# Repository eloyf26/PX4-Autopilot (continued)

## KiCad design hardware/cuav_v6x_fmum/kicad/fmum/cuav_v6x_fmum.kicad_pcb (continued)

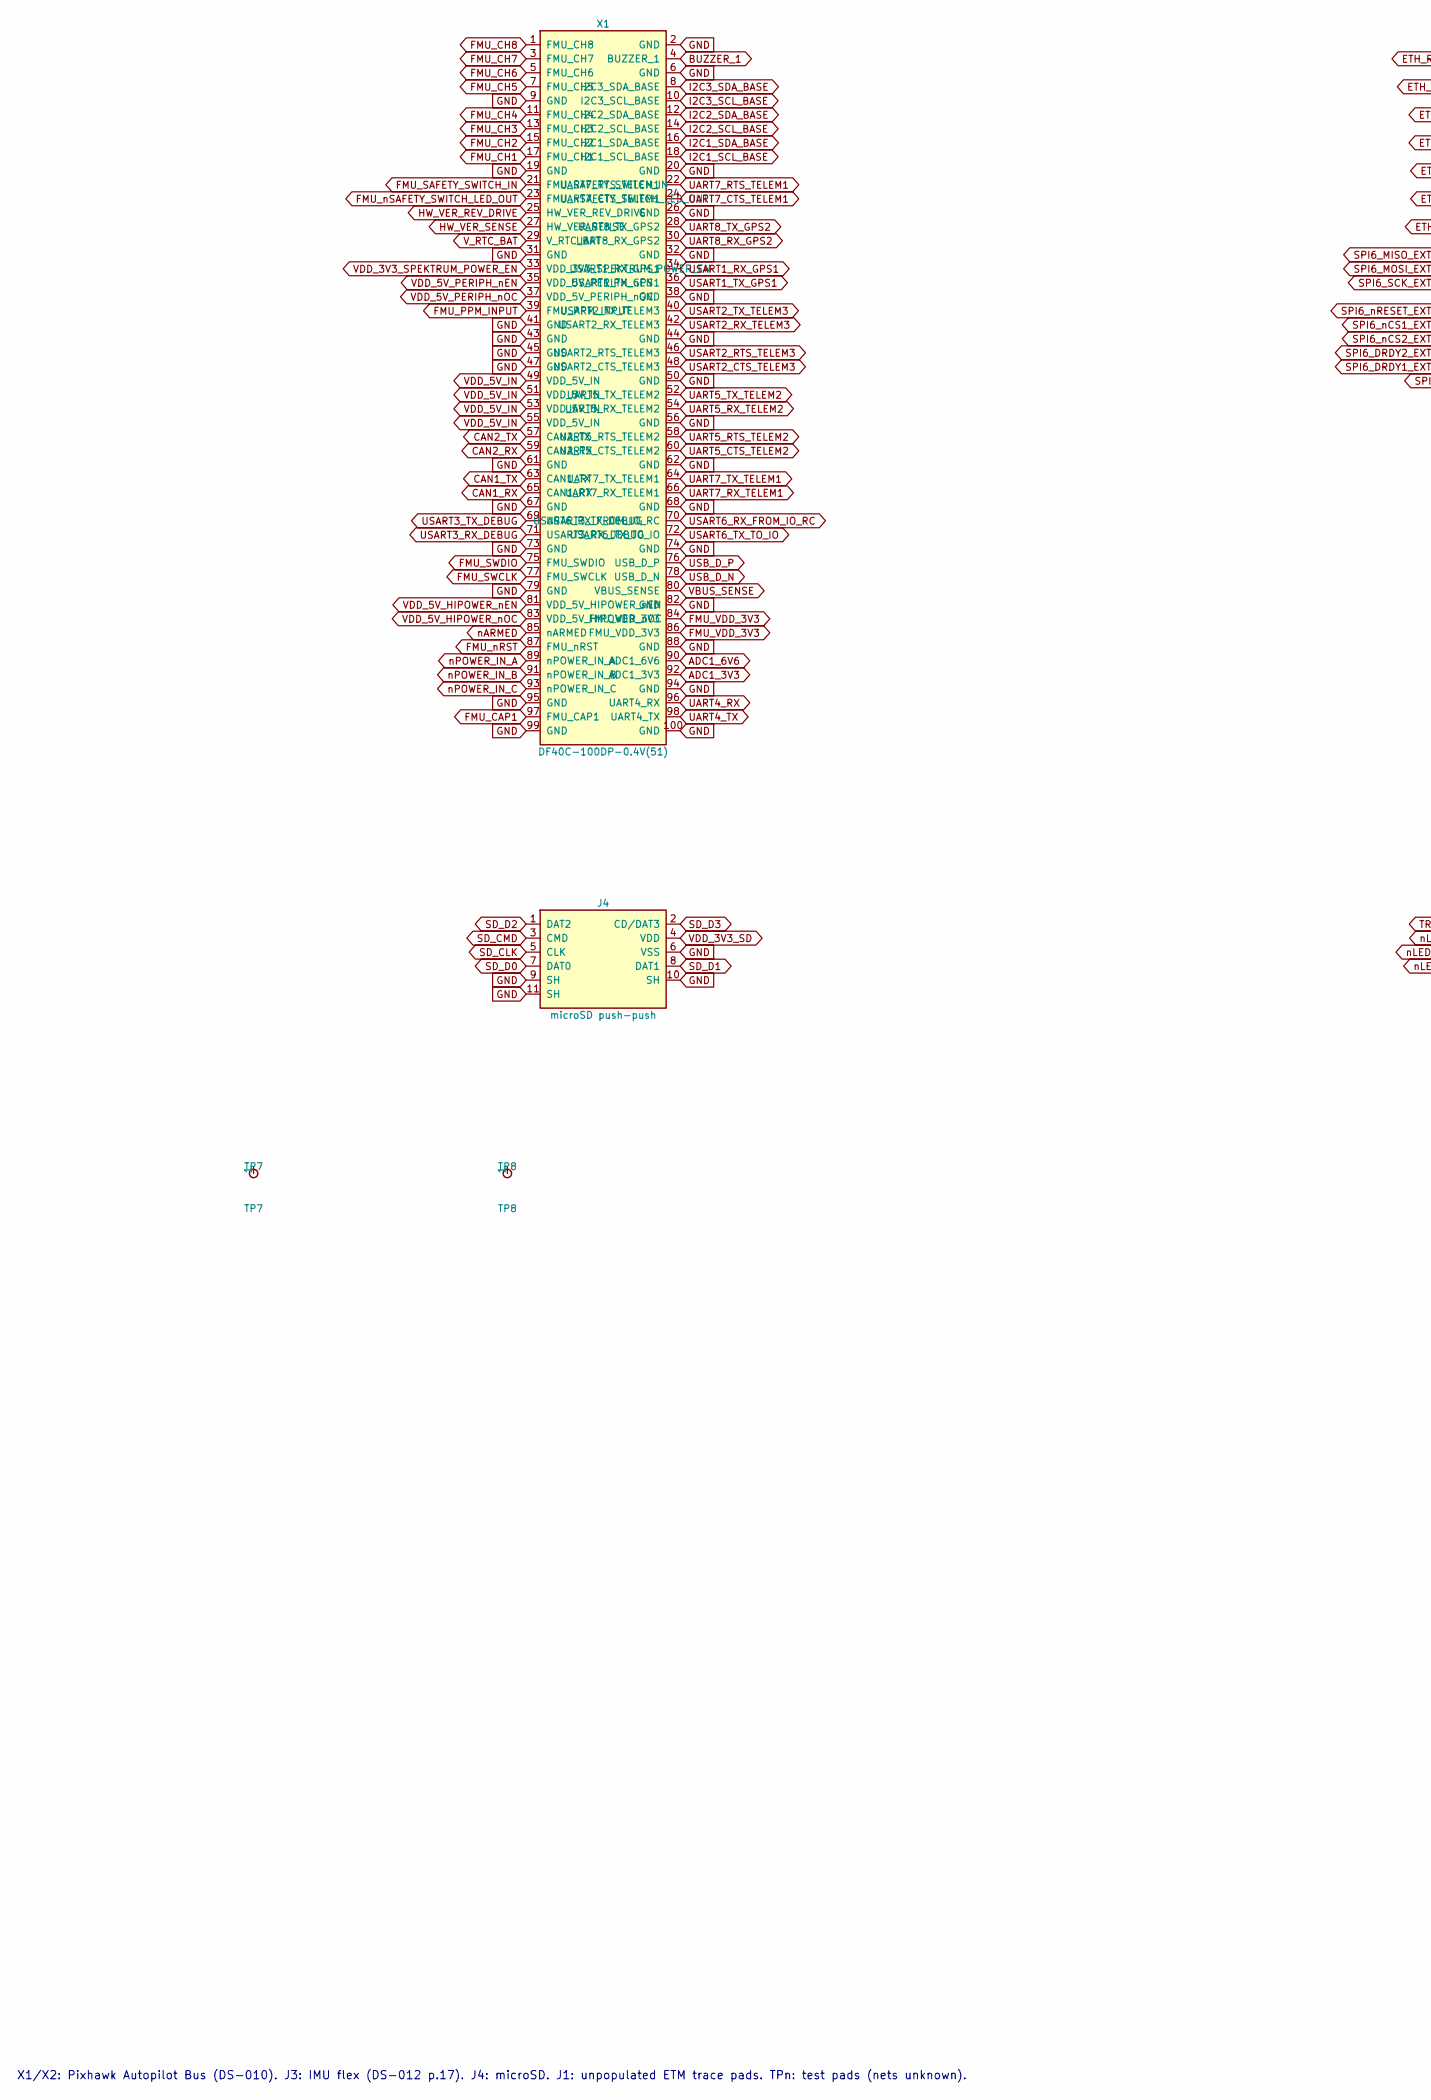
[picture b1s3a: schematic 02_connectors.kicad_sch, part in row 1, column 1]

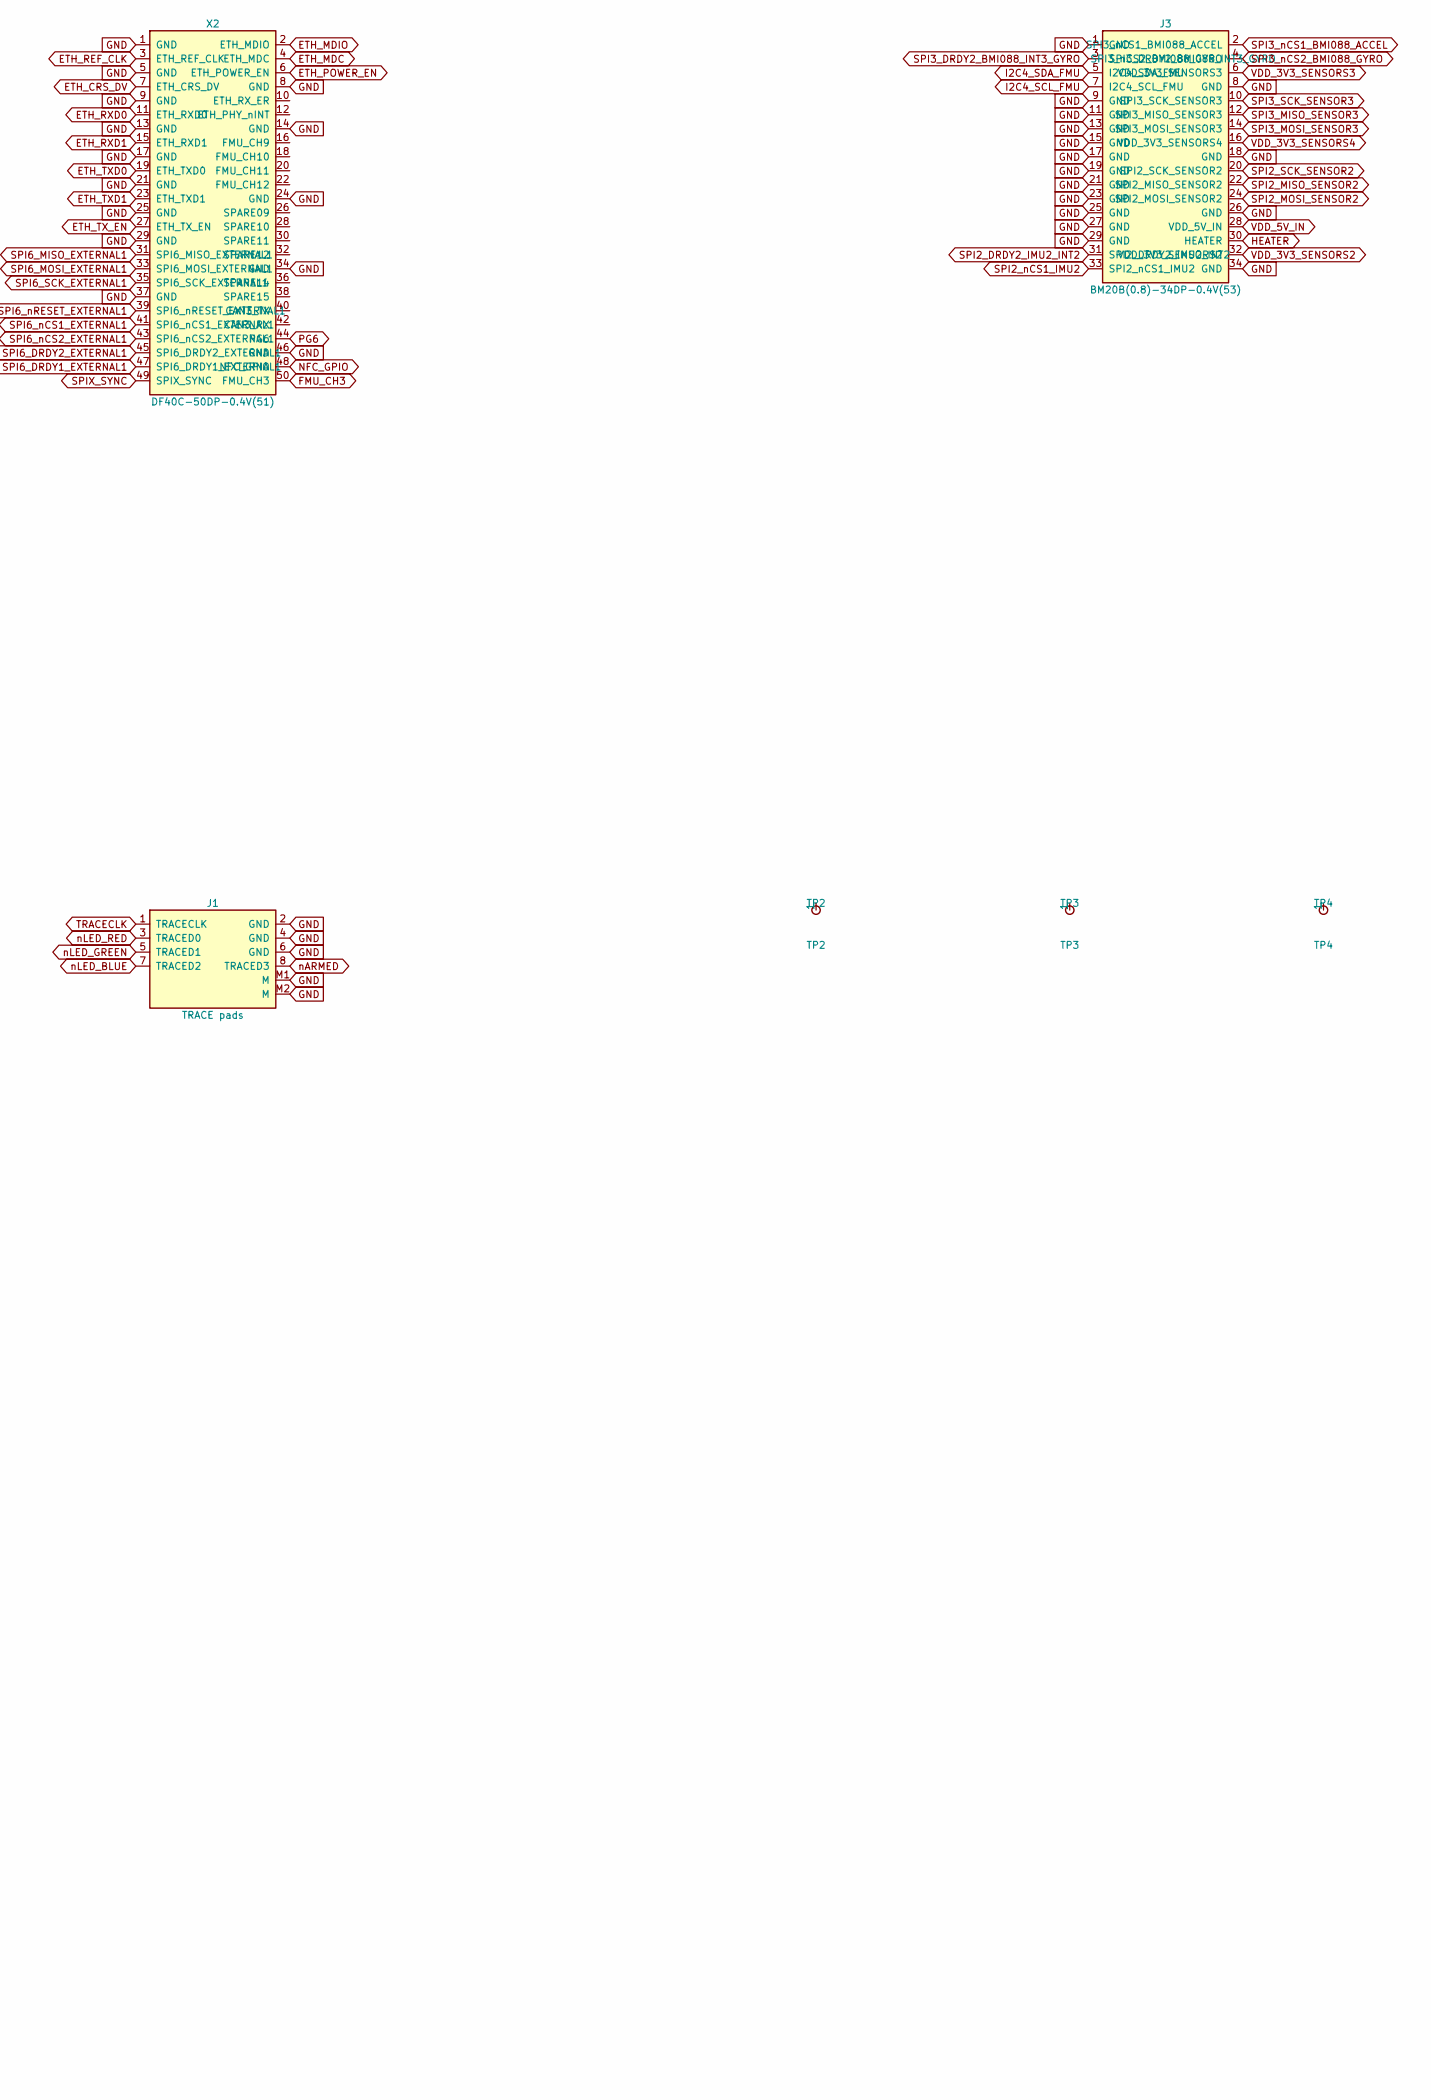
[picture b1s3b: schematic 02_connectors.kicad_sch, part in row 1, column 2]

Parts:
J1: TRACE pads; TRACE_8+2
J3: BM20B(0.8)-34DP-0.4V(53); Hirose_BM20B-34-0.4V
J4: microSD push-push; microSD_HC_Molex_104031-0811
TP2: TP2; TestPad_1.0mm
TP3: TP3; TestPad_1.0mm
TP4: TP4; TestPad_1.0mm
TP7: TP7; TestPad_1.0mm
TP8: TP8; TestPad_1.0mm
X1: DF40C-100DP-0.4V(51); Hirose_DF40C-100DP-0.4V
X2: DF40C-50DP-0.4V(51); Hirose_DF40C-50DP-0.4V

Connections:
ADC1_3V3: X1.92 (ADC1_3V3); also elsewhere on the board
ADC1_6V6: X1.90 (ADC1_6V6); also elsewhere on the board
BUZZER_1: X1.4 (BUZZER_1); also elsewhere on the board
CAN1_RX: X1.65 (CAN1_RX); also elsewhere on the board
CAN1_TX: X1.63 (CAN1_TX); also elsewhere on the board
CAN2_RX: X1.59 (CAN2_RX); also elsewhere on the board
CAN2_TX: X1.57 (CAN2_TX); also elsewhere on the board
ETH_CRS_DV: X2.7 (ETH_CRS_DV); also elsewhere on the board
ETH_MDC: X2.4 (ETH_MDC); also elsewhere on the board
ETH_MDIO: X2.2 (ETH_MDIO); also elsewhere on the board
ETH_POWER_EN: X2.6 (ETH_POWER_EN); also elsewhere on the board
ETH_REF_CLK: X2.3 (ETH_REF_CLK); also elsewhere on the board
ETH_RXD0: X2.11 (ETH_RXD0); also elsewhere on the board
ETH_RXD1: X2.15 (ETH_RXD1); also elsewhere on the board
ETH_TXD0: X2.19 (ETH_TXD0); also elsewhere on the board
ETH_TXD1: X2.23 (ETH_TXD1); also elsewhere on the board
ETH_TX_EN: X2.27 (ETH_TX_EN); also elsewhere on the board
FMU_CAP1: X1.97 (FMU_CAP1); also elsewhere on the board
FMU_CH1: X1.17 (FMU_CH1); also elsewhere on the board
FMU_CH2: X1.15 (FMU_CH2); also elsewhere on the board
FMU_CH3: X1.13 (FMU_CH3), X2.50 (FMU_CH3); also elsewhere on the board
FMU_CH4: X1.11 (FMU_CH4); also elsewhere on the board
FMU_CH5: X1.7 (FMU_CH5); also elsewhere on the board
FMU_CH6: X1.5 (FMU_CH6); also elsewhere on the board
FMU_CH7: X1.3 (FMU_CH7); also elsewhere on the board
FMU_CH8: X1.1 (FMU_CH8); also elsewhere on the board
FMU_PPM_INPUT: X1.39 (FMU_PPM_INPUT); also elsewhere on the board
FMU_SAFETY_SWITCH_IN: X1.21 (FMU_SAFETY_SWITCH_IN); also elsewhere on the board
FMU_SWCLK: X1.77 (FMU_SWCLK); also elsewhere on the board
FMU_SWDIO: X1.75 (FMU_SWDIO); also elsewhere on the board
FMU_VDD_3V3: X1.84 (FMU_VDD_3V3), X1.86 (FMU_VDD_3V3); also elsewhere on the board
FMU_nRST: X1.87 (FMU_nRST); also elsewhere on the board
FMU_nSAFETY_SWITCH_LED_OUT: X1.23 (FMU_nSAFETY_SWITCH_LED_OUT); also elsewhere on the board
GND: J1.2 (GND), J1.4 (GND), J1.6 (GND), J1.M1 (M), J1.M2 (M), J3.1 (GND), J3.8 (GND), J3.9 (GND), J3.11 (GND), J3.13 (GND), J3.15 (GND), J3.17 (GND), J3.18 (GND), J3.19 (GND), J3.21 (GND), J3.23 (GND), J3.25 (GND), J3.26 (GND), J3.27 (GND), J3.29 (GND), J3.34 (GND), J4.6 (VSS), J4.9 (SH), J4.10 (SH), J4.11 (SH), X1.2 (GND), X1.6 (GND), X1.9 (GND), X1.19 (GND), X1.20 (GND), X1.26 (GND), X1.31 (GND), X1.32 (GND), X1.38 (GND), X1.41 (GND), X1.43 (GND), X1.44 (GND), X1.45 (GND), X1.47 (GND), X1.50 (GND), X1.56 (GND), X1.61 (GND), X1.62 (GND), X1.67 (GND), X1.68 (GND), X1.73 (GND), X1.74 (GND), X1.79 (GND), X1.82 (GND), X1.88 (GND), X1.94 (GND), X1.95 (GND), X1.99 (GND), X1.100 (GND), X2.1 (GND), X2.5 (GND), X2.8 (GND), X2.9 (GND), X2.13 (GND), X2.14 (GND), X2.17 (GND), X2.21 (GND), X2.24 (GND), X2.25 (GND), X2.29 (GND), X2.34 (GND), X2.37 (GND), X2.46 (GND); also elsewhere on the board
HEATER: J3.30 (HEATER); also elsewhere on the board
HW_VER_REV_DRIVE: X1.25 (HW_VER_REV_DRIVE); also elsewhere on the board
HW_VER_SENSE: X1.27 (HW_VER_SENSE); also elsewhere on the board
I2C1_SCL_BASE: X1.18 (I2C1_SCL_BASE); also elsewhere on the board
I2C1_SDA_BASE: X1.16 (I2C1_SDA_BASE); also elsewhere on the board
I2C2_SCL_BASE: X1.14 (I2C2_SCL_BASE); also elsewhere on the board
I2C2_SDA_BASE: X1.12 (I2C2_SDA_BASE); also elsewhere on the board
I2C3_SCL_BASE: X1.10 (I2C3_SCL_BASE); also elsewhere on the board
I2C3_SDA_BASE: X1.8 (I2C3_SDA_BASE); also elsewhere on the board
I2C4_SCL_FMU: J3.7 (I2C4_SCL_FMU); also elsewhere on the board
I2C4_SDA_FMU: J3.5 (I2C4_SDA_FMU); also elsewhere on the board
NFC_GPIO: X2.48 (NFC_GPIO); also elsewhere on the board
PG6: X2.44 (PG6); also elsewhere on the board
SD_CLK: J4.5 (CLK); also elsewhere on the board
SD_CMD: J4.3 (CMD); also elsewhere on the board
SD_D0: J4.7 (DAT0); also elsewhere on the board
SD_D1: J4.8 (DAT1); also elsewhere on the board
SD_D2: J4.1 (DAT2); also elsewhere on the board
SD_D3: J4.2 (CD/DAT3); also elsewhere on the board
SPI2_DRDY2_IMU2_INT2: J3.31 (SPI2_DRDY2_IMU2_INT2); also elsewhere on the board
SPI2_MISO_SENSOR2: J3.22 (SPI2_MISO_SENSOR2); also elsewhere on the board
SPI2_MOSI_SENSOR2: J3.24 (SPI2_MOSI_SENSOR2); also elsewhere on the board
SPI2_SCK_SENSOR2: J3.20 (SPI2_SCK_SENSOR2); also elsewhere on the board
SPI2_nCS1_IMU2: J3.33 (SPI2_nCS1_IMU2); also elsewhere on the board
SPI3_DRDY2_BMI088_INT3_GYRO: J3.3 (SPI3_DRDY2_BMI088_INT3_GYRO); also elsewhere on the board
SPI3_MISO_SENSOR3: J3.12 (SPI3_MISO_SENSOR3); also elsewhere on the board
SPI3_MOSI_SENSOR3: J3.14 (SPI3_MOSI_SENSOR3); also elsewhere on the board
SPI3_SCK_SENSOR3: J3.10 (SPI3_SCK_SENSOR3); also elsewhere on the board
SPI3_nCS1_BMI088_ACCEL: J3.2 (SPI3_nCS1_BMI088_ACCEL); also elsewhere on the board
SPI3_nCS2_BMI088_GYRO: J3.4 (SPI3_nCS2_BMI088_GYRO); also elsewhere on the board
SPI6_DRDY1_EXTERNAL1: X2.47 (SPI6_DRDY1_EXTERNAL1); also elsewhere on the board
SPI6_DRDY2_EXTERNAL1: X2.45 (SPI6_DRDY2_EXTERNAL1); also elsewhere on the board
SPI6_MISO_EXTERNAL1: X2.31 (SPI6_MISO_EXTERNAL1); also elsewhere on the board
SPI6_MOSI_EXTERNAL1: X2.33 (SPI6_MOSI_EXTERNAL1); also elsewhere on the board
SPI6_SCK_EXTERNAL1: X2.35 (SPI6_SCK_EXTERNAL1); also elsewhere on the board
SPI6_nCS1_EXTERNAL1: X2.41 (SPI6_nCS1_EXTERNAL1); also elsewhere on the board
SPI6_nCS2_EXTERNAL1: X2.43 (SPI6_nCS2_EXTERNAL1); also elsewhere on the board
SPI6_nRESET_EXTERNAL1: X2.39 (SPI6_nRESET_EXTERNAL1); also elsewhere on the board
SPIX_SYNC: X2.49 (SPIX_SYNC); also elsewhere on the board
TRACECLK: J1.1 (TRACECLK); also elsewhere on the board
UART4_RX: X1.96 (UART4_RX); also elsewhere on the board
UART4_TX: X1.98 (UART4_TX); also elsewhere on the board
UART5_CTS_TELEM2: X1.60 (UART5_CTS_TELEM2); also elsewhere on the board
UART5_RTS_TELEM2: X1.58 (UART5_RTS_TELEM2); also elsewhere on the board
UART5_RX_TELEM2: X1.54 (UART5_RX_TELEM2); also elsewhere on the board
UART5_TX_TELEM2: X1.52 (UART5_TX_TELEM2); also elsewhere on the board
UART7_CTS_TELEM1: X1.24 (UART7_CTS_TELEM1); also elsewhere on the board
UART7_RTS_TELEM1: X1.22 (UART7_RTS_TELEM1); also elsewhere on the board
UART7_RX_TELEM1: X1.66 (UART7_RX_TELEM1); also elsewhere on the board
UART7_TX_TELEM1: X1.64 (UART7_TX_TELEM1); also elsewhere on the board
UART8_RX_GPS2: X1.30 (UART8_RX_GPS2); also elsewhere on the board
UART8_TX_GPS2: X1.28 (UART8_TX_GPS2); also elsewhere on the board
USART1_RX_GPS1: X1.34 (USART1_RX_GPS1); also elsewhere on the board
USART1_TX_GPS1: X1.36 (USART1_TX_GPS1); also elsewhere on the board
USART2_CTS_TELEM3: X1.48 (USART2_CTS_TELEM3); also elsewhere on the board
USART2_RTS_TELEM3: X1.46 (USART2_RTS_TELEM3); also elsewhere on the board
USART2_RX_TELEM3: X1.42 (USART2_RX_TELEM3); also elsewhere on the board
USART2_TX_TELEM3: X1.40 (USART2_TX_TELEM3); also elsewhere on the board
USART3_RX_DEBUG: X1.71 (USART3_RX_DEBUG); also elsewhere on the board
USART3_TX_DEBUG: X1.69 (USART3_TX_DEBUG); also elsewhere on the board
USART6_RX_FROM_IO_RC: X1.70 (USART6_RX_FROM_IO_RC); also elsewhere on the board
USART6_TX_TO_IO: X1.72 (USART6_TX_TO_IO); also elsewhere on the board
USB_D_N: X1.78 (USB_D_N); also elsewhere on the board
USB_D_P: X1.76 (USB_D_P); also elsewhere on the board
VBUS_SENSE: X1.80 (VBUS_SENSE); also elsewhere on the board
VDD_3V3_SD: J4.4 (VDD); also elsewhere on the board
VDD_3V3_SENSORS2: J3.32 (VDD_3V3_SENSORS2); also elsewhere on the board
VDD_3V3_SENSORS3: J3.6 (VDD_3V3_SENSORS3); also elsewhere on the board
VDD_3V3_SENSORS4: J3.16 (VDD_3V3_SENSORS4); also elsewhere on the board
VDD_3V3_SPEKTRUM_POWER_EN: X1.33 (VDD_3V3_SPEKTRUM_POWER_EN); also elsewhere on the board
VDD_5V_HIPOWER_nEN: X1.81 (VDD_5V_HIPOWER_nEN); also elsewhere on the board
VDD_5V_HIPOWER_nOC: X1.83 (VDD_5V_HIPOWER_nOC); also elsewhere on the board
VDD_5V_IN: J3.28 (VDD_5V_IN), X1.49 (VDD_5V_IN), X1.51 (VDD_5V_IN), X1.53 (VDD_5V_IN), X1.55 (VDD_5V_IN); also elsewhere on the board
VDD_5V_PERIPH_nEN: X1.35 (VDD_5V_PERIPH_nEN); also elsewhere on the board
VDD_5V_PERIPH_nOC: X1.37 (VDD_5V_PERIPH_nOC); also elsewhere on the board
V_RTC_BAT: X1.29 (V_RTC_BAT); also elsewhere on the board
nARMED: J1.8 (TRACED3), X1.85 (nARMED); also elsewhere on the board
nLED_BLUE: J1.7 (TRACED2); also elsewhere on the board
nLED_GREEN: J1.5 (TRACED1); also elsewhere on the board
nLED_RED: J1.3 (TRACED0); also elsewhere on the board
nPOWER_IN_A: X1.89 (nPOWER_IN_A); also elsewhere on the board
nPOWER_IN_B: X1.91 (nPOWER_IN_B); also elsewhere on the board
nPOWER_IN_C: X1.93 (nPOWER_IN_C); also elsewhere on the board

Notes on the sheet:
X1/X2: Pixhawk Autopilot Bus (DS-010). J3: IMU flex (DS-012 p.17). J4: microSD. J1: unpopulated ETM trace pads. TPn: test pads (nets unknown).

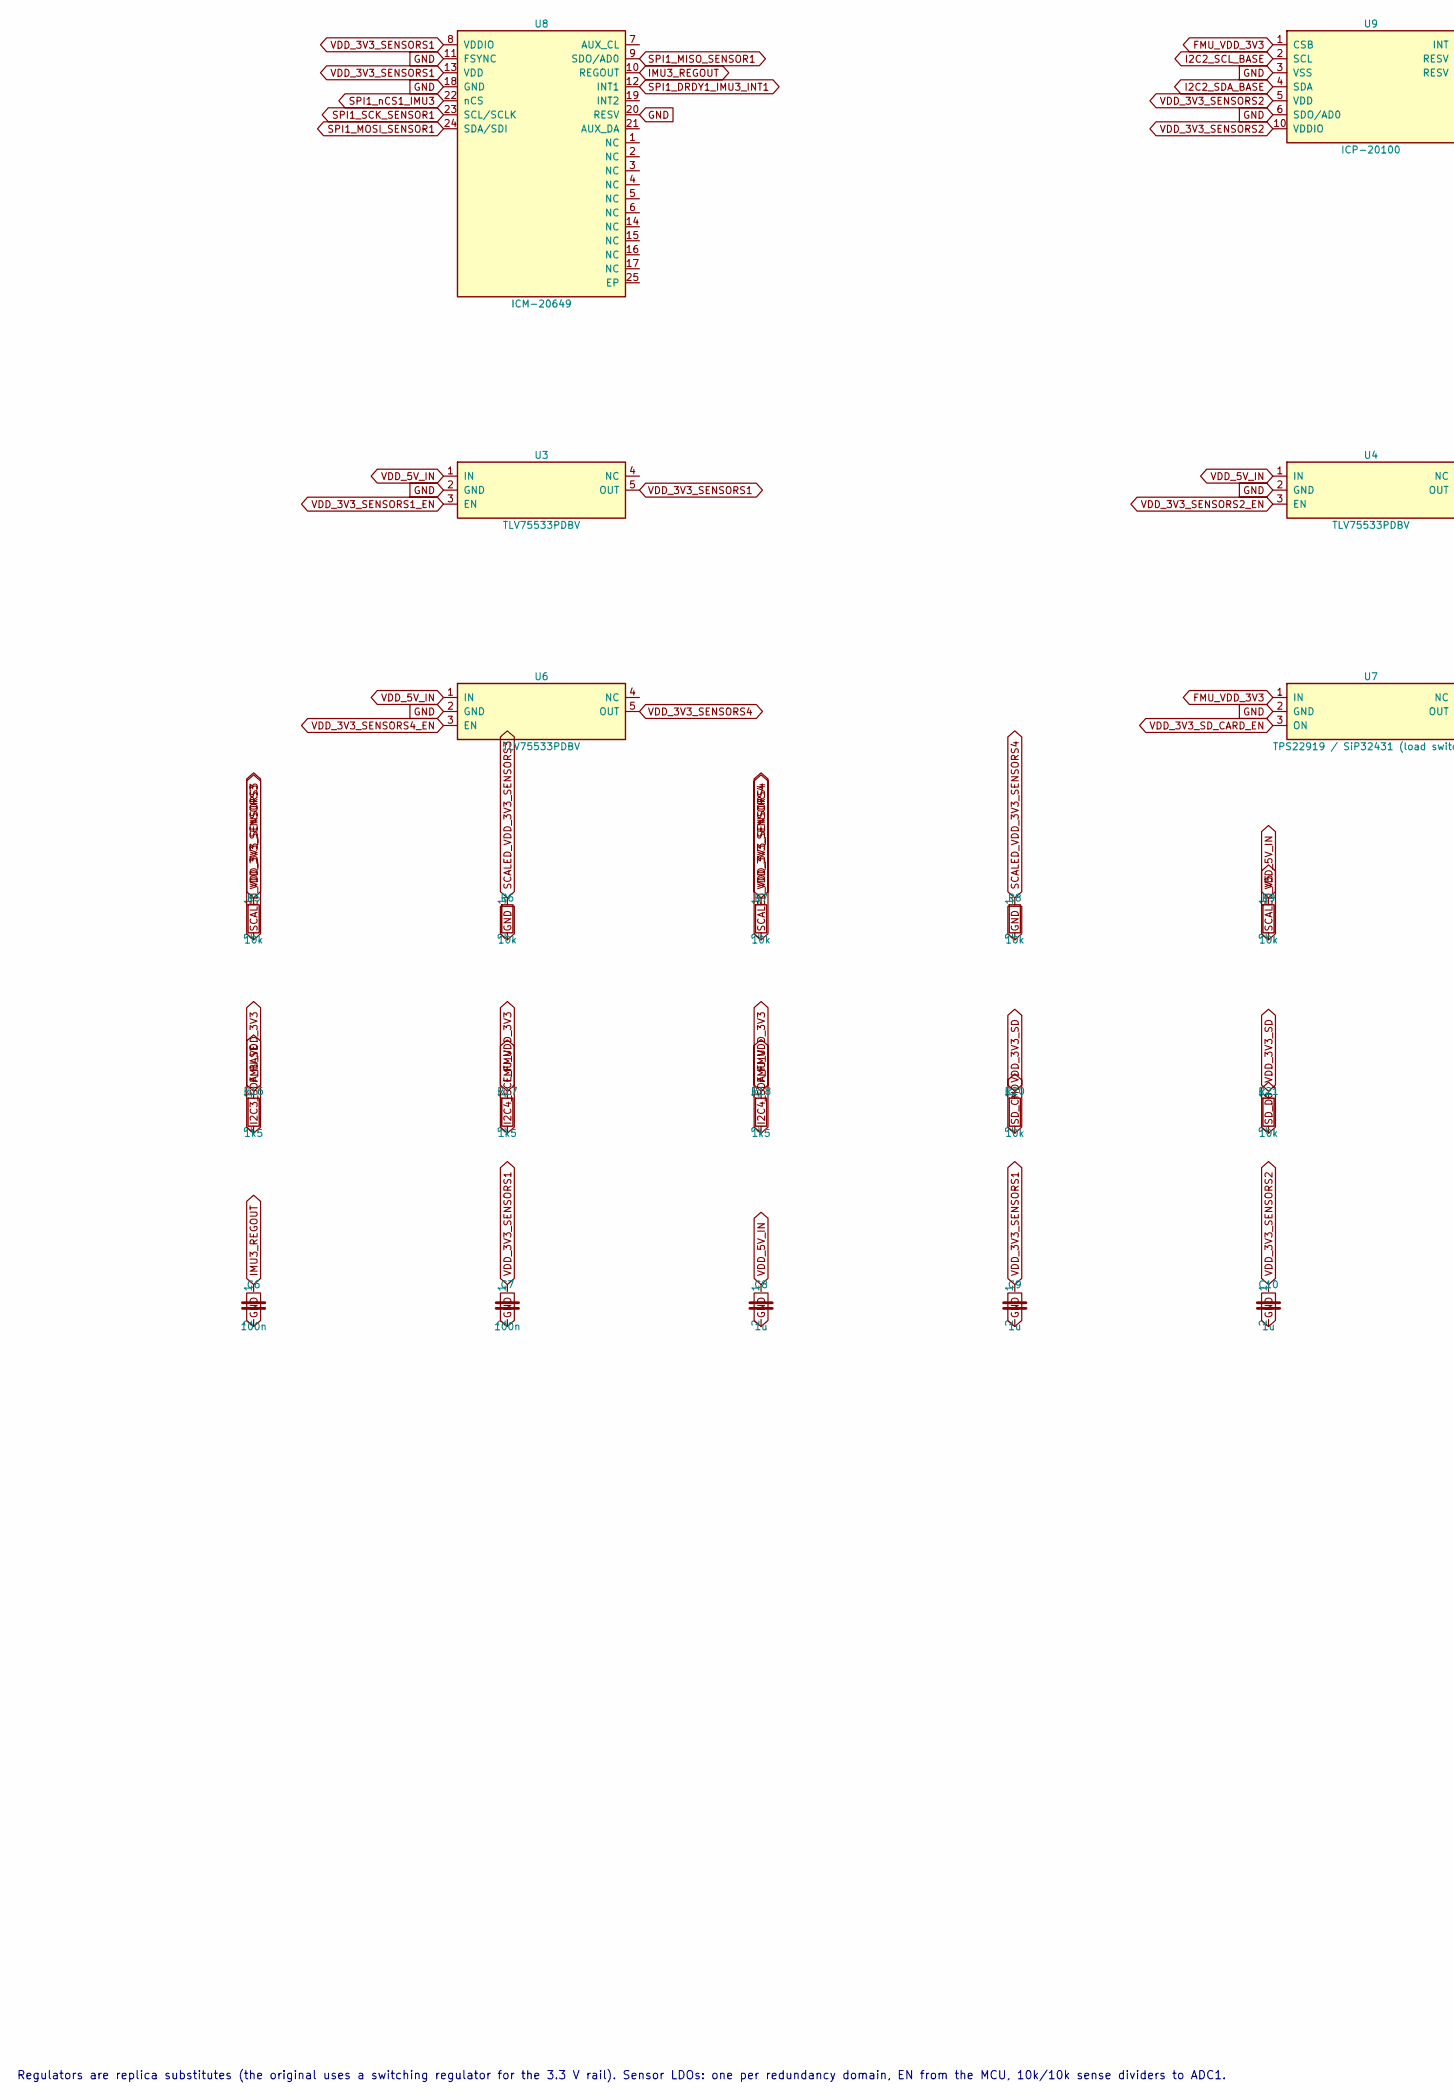
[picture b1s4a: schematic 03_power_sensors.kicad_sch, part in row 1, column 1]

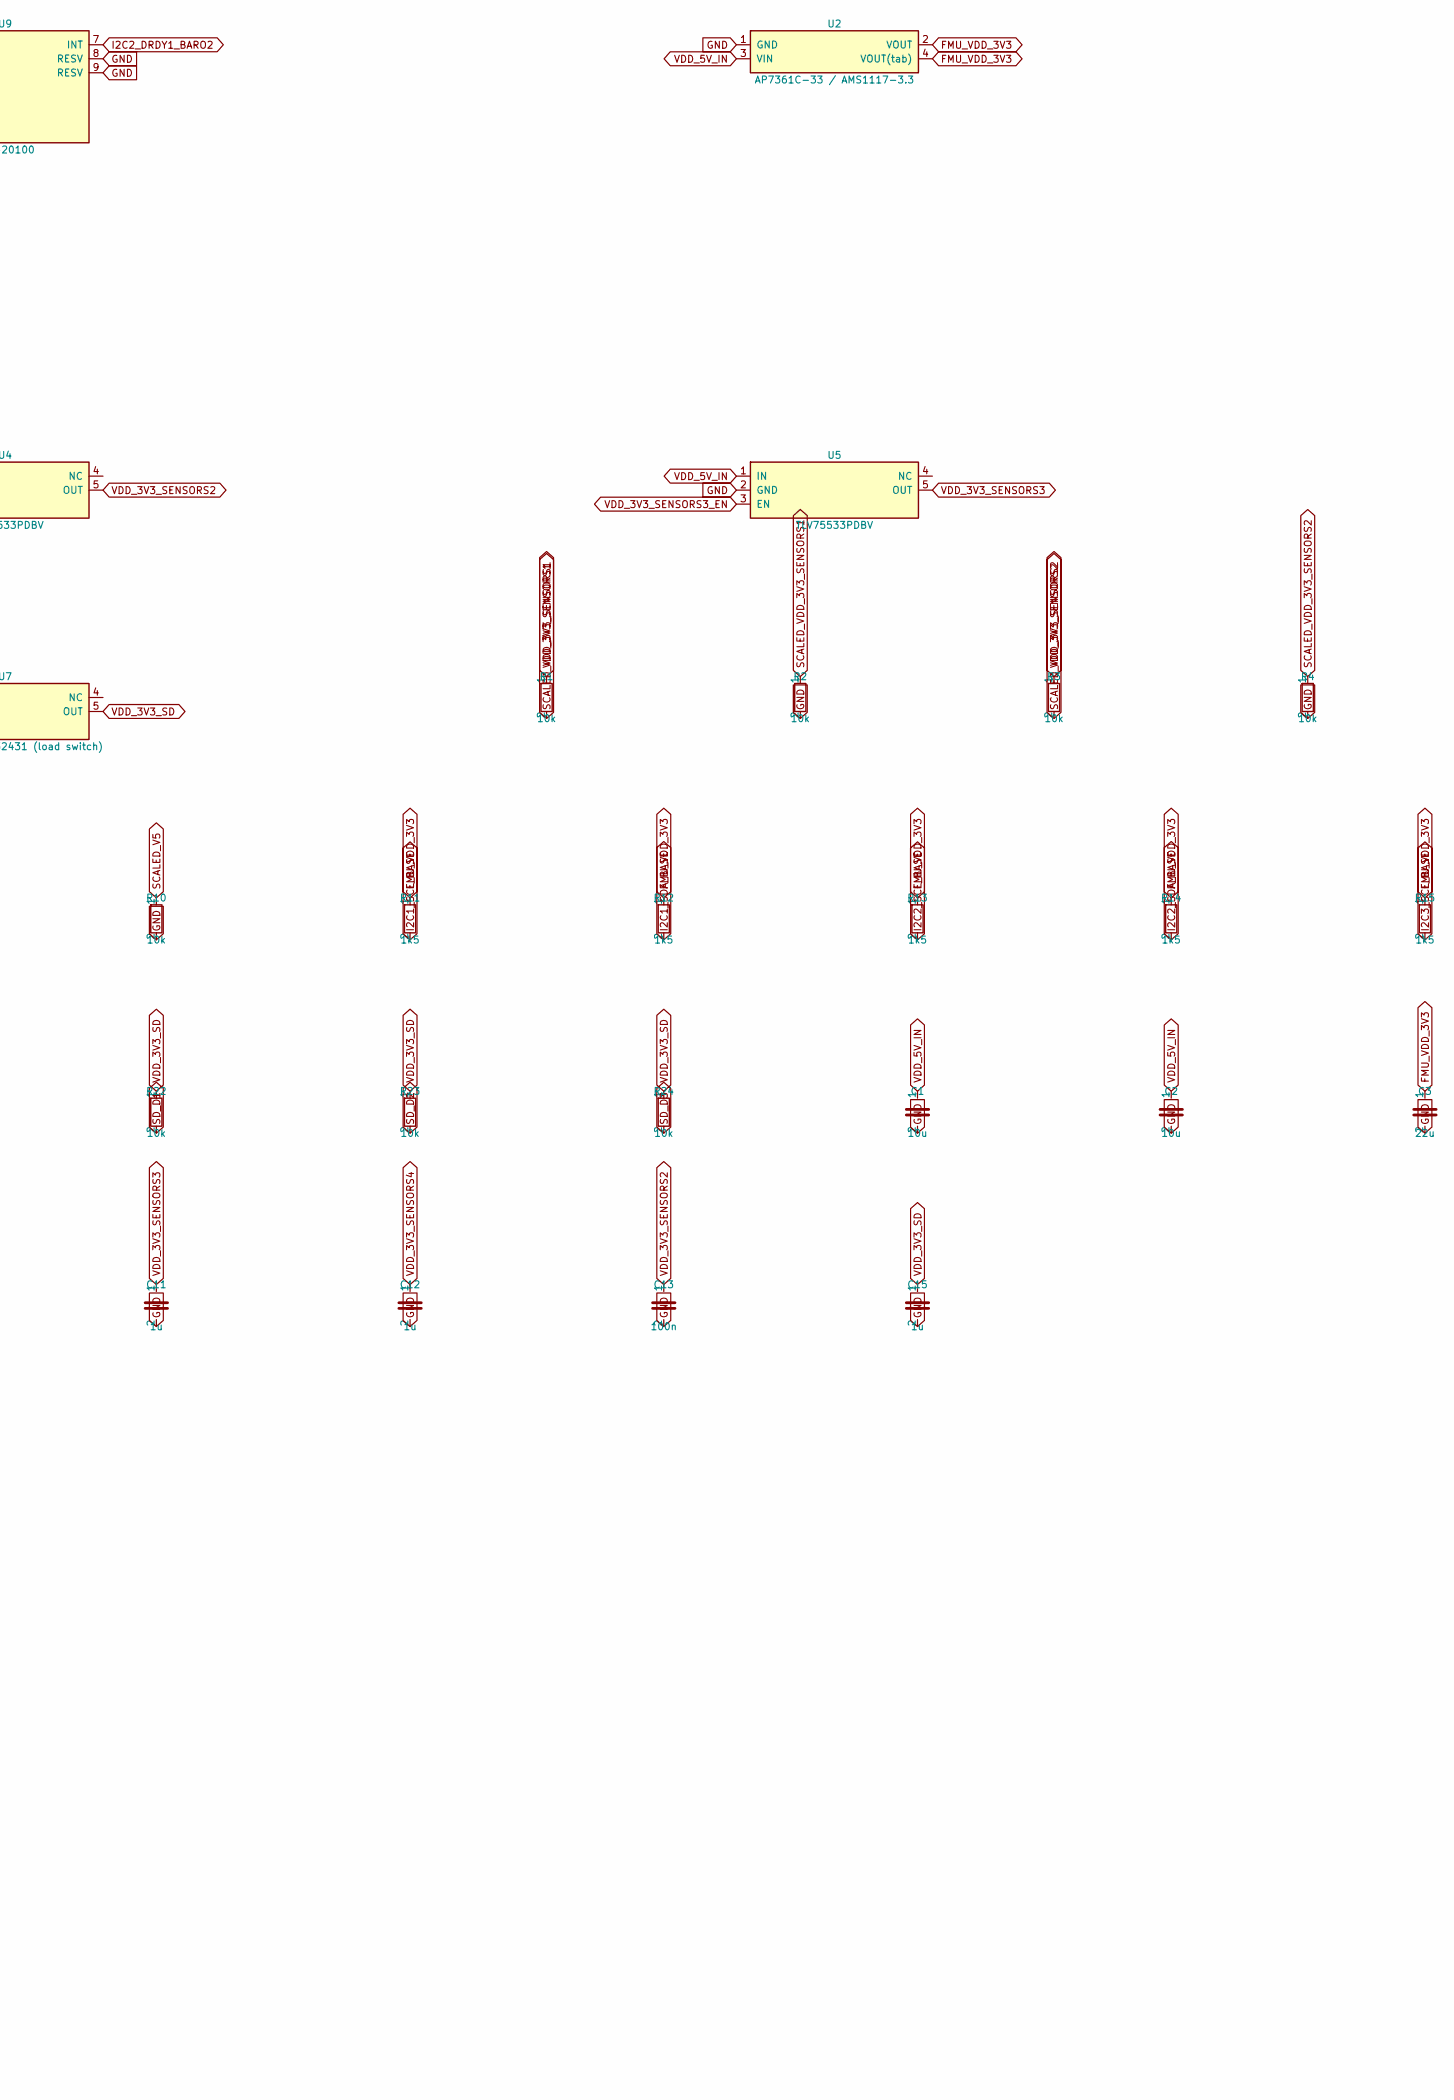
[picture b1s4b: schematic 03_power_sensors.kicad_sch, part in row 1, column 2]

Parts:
C1, C2: 10u; C_0603_1608Metric
C3: 22u; C_0805_2012Metric
C6, C7, C13: 100n; C_0402_1005Metric
C8, C9, C10, C11, C12, C15: 1u; C_0402_1005Metric
R1, R2, R3, R4, R5, R6, R7, R8, R9, R10, R20, R21, R22, R23, R24: 10k; R_0402_1005Metric
R11, R12, R13, R14, R15, R16, R17, R18: 1k5; R_0402_1005Metric
U2: AP7361C-33 / AMS1117-3.3; SOT-223-3_TabPin2
U3, U4, U5, U6: TLV75533PDBV; SOT-23-5
U7: TPS22919 / SiP32431 (load switch); SOT-23-5
U8: ICM-20649; QFN-24-1EP_3x3mm_P0.4mm_EP1.75x1.6mm
U9: ICP-20100; TDK_LGA-10_2x2mm_P0.5mm

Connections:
FMU_VDD_3V3: C3.1, R11.1, R12.1, R13.1, R14.1, R15.1, R16.1, R17.1, R18.1, U2.2 (VOUT), U2.4 (VOUT(tab)), U7.1 (IN), U9.1 (CSB); also elsewhere on the board
GND: C1.2, C2.2, C3.2, C6.2, C7.2, C8.2, C9.2, C10.2, C11.2, C12.2, C13.2, C15.2, R2.2, R4.2, R6.2, R8.2, R10.2, U2.1 (GND), U3.2 (GND), U4.2 (GND), U5.2 (GND), U6.2 (GND), U7.2 (GND), U8.11 (FSYNC), U8.18 (GND), U8.20 (RESV), U9.3 (VSS), U9.6 (SDO/AD0), U9.8 (RESV), U9.9 (RESV); also elsewhere on the board
I2C1_SCL_BASE: R11.2; also elsewhere on the board
I2C1_SDA_BASE: R12.2; also elsewhere on the board
I2C2_DRDY1_BARO2: U9.7 (INT); also elsewhere on the board
I2C2_SCL_BASE: R13.2, U9.2 (SCL); also elsewhere on the board
I2C2_SDA_BASE: R14.2, U9.4 (SDA); also elsewhere on the board
I2C3_SCL_BASE: R15.2; also elsewhere on the board
I2C3_SDA_BASE: R16.2; also elsewhere on the board
I2C4_SCL_FMU: R17.2; also elsewhere on the board
I2C4_SDA_FMU: R18.2; also elsewhere on the board
IMU3_REGOUT: C6.1, U8.10 (REGOUT)
SCALED_V5: R9.2, R10.1; also elsewhere on the board
SCALED_VDD_3V3_SENSORS1: R1.2, R2.1; also elsewhere on the board
SCALED_VDD_3V3_SENSORS2: R3.2, R4.1; also elsewhere on the board
SCALED_VDD_3V3_SENSORS3: R5.2, R6.1; also elsewhere on the board
SCALED_VDD_3V3_SENSORS4: R7.2, R8.1; also elsewhere on the board
SD_CMD: R20.2; also elsewhere on the board
SD_D0: R21.2; also elsewhere on the board
SD_D1: R22.2; also elsewhere on the board
SD_D2: R23.2; also elsewhere on the board
SD_D3: R24.2; also elsewhere on the board
SPI1_DRDY1_IMU3_INT1: U8.12 (INT1); also elsewhere on the board
SPI1_MISO_SENSOR1: U8.9 (SDO/AD0); also elsewhere on the board
SPI1_MOSI_SENSOR1: U8.24 (SDA/SDI); also elsewhere on the board
SPI1_SCK_SENSOR1: U8.23 (SCL/SCLK); also elsewhere on the board
SPI1_nCS1_IMU3: U8.22 (nCS); also elsewhere on the board
VDD_3V3_SD: C15.1, R20.1, R21.1, R22.1, R23.1, R24.1, U7.5 (OUT); also elsewhere on the board
VDD_3V3_SD_CARD_EN: U7.3 (ON); also elsewhere on the board
VDD_3V3_SENSORS1: C7.1, C9.1, R1.1, U3.5 (OUT), U8.8 (VDDIO), U8.13 (VDD)
VDD_3V3_SENSORS1_EN: U3.3 (EN); also elsewhere on the board
VDD_3V3_SENSORS2: C10.1, C13.1, R3.1, U4.5 (OUT), U9.5 (VDD), U9.10 (VDDIO); also elsewhere on the board
VDD_3V3_SENSORS2_EN: U4.3 (EN); also elsewhere on the board
VDD_3V3_SENSORS3: C11.1, R5.1, U5.5 (OUT); also elsewhere on the board
VDD_3V3_SENSORS3_EN: U5.3 (EN); also elsewhere on the board
VDD_3V3_SENSORS4: C12.1, R7.1, U6.5 (OUT); also elsewhere on the board
VDD_3V3_SENSORS4_EN: U6.3 (EN); also elsewhere on the board
VDD_5V_IN: C1.1, C2.1, C8.1, R9.1, U2.3 (VIN), U3.1 (IN), U4.1 (IN), U5.1 (IN), U6.1 (IN); also elsewhere on the board

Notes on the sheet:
Regulators are replica substitutes (the original uses a switching regulator for the 3.3 V rail). Sensor LDOs: one per redundancy domain, EN from the MCU, 10k/10k sense dividers to ADC1.
